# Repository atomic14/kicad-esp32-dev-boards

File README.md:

# ESP Dev-Board Generator

Generates canonical "basic dev board" KiCad schematics for the Espressif modules
that have a **PCB antenna + native USB** (12 modules across S2/S3/C3/C5/C6/H2).
Each board takes a shared skeleton (USB-C, 3V3 LDO, BOOT/EN buttons, LEDs) and
adds the module symbol + two break-out pin headers, wired entirely with net
labels (no routing). Output is a complete, openable KiCad project per module.

> **Why / design rationale:** see [`DECISIONS.md`](DECISIONS.md). This file is
> the *operational* guide; DECISIONS.md is the *why*.

## What it builds

Every board is the same canonical dev board — USB-C, 3V3 LDO, BOOT/EN buttons,
power + user LEDs — plus the module and its full GPIO break-out on two headers
(that's the ESP32-C3-WROOM-02 above; every component carries its 3D model, so
each board renders assembly-ready). The views below are to scale (equal
mm-per-pixel; each label carries the board's WxH):

The back silk labels every header pin with its net name and carries a vertical
board identifier — the module name plus the git revision that generated it
(`git describe --tags --always --dirty`):

These are snapshots of what `make.py --render` writes to `build/`: seven
montages (`montage_{top,top_bare,bottom}[_scale].png` — auto-fit and to-scale —
plus `montage_hero.png`) and a perspective `render_hero.png` per board under
`build/<MODULE>/`. To refresh them:

```bash
cp build/montage_{top,bottom}_scale.png docs/images/
cp build/ESP32-C3-WROOM-02/render_hero.png docs/images/hero.png
```

`make.py --animate` adds the moving version: `build/montage_spin.mp4`, a
2560×1440 grid of all 12 boards each turning a full 360° on a three-quarter
tilt, staggered so the grid reads as a wave. The turn wraps exactly, so it
loops seamlessly. It renders ~1440 frames and takes roughly half an hour —
`--frames`/`--supersample` trade quality for time, and `--boards X --grid 1x1`
renders a single board full-frame.

## Prerequisites (per machine)

1. **KiCad 10.x** installed (the schematics use the v10 file format).
2. **Espressif KiCad libraries installed *for that same KiCad version*** via
   KiCad's **Plug-in & Content Manager** (open KiCad 10 → PCM → search
   "Espressif" → install "Espressif KiCad Libraries" → Apply). This provides the
   `PCM_Espressif` symbol/footprint libraries. *This is the one manual install
   step and must be done before running anything.*
   > ⚠️ The addon is installed **per KiCad major version**. Having it for
   > KiCad 8/9 does **not** count if you run KiCad 10 — the PCM stores each
   > version's addons under a separate `Documents/KiCad/<version>/3rdparty` dir.
   > `resolve_library.py` pins to your running `kicad-cli` version and will
   > **hard-fail** (with these instructions) if the addon is missing for it,
   > rather than silently mixing libraries across versions.
3. **[uv](https://docs.astral.sh/uv/)** (Python package manager).
4. **[KiCadRoutingTools](https://github.com/atomic14/KiCadRoutingTools)** (our
   fork, `dev-board-fixes` branch) cloned as a **sibling** of this repo (or set
   `$KICAD_ROUTING_TOOLS`), with its Rust router built:
   ```bash
   git clone -b dev-board-fixes https://github.com/atomic14/KiCadRoutingTools.git ../KiCadRoutingTools
   (cd ../KiCadRoutingTools && python3 build_router.py --from-source)  # needs cargo
   ```
   Only needed for the *route* stage — build/render/fab work without it.
5. Internet access to `https://www.atomic14.com/esp32/` (only needed when
   curating a new module's `board.yaml`).

`resolve_library.py` auto-locates KiCad on macOS / Linux / Windows. If it can't,
set `ESPRESSIF_3RDPARTY` (the `<kicad>/3rdparty` dir) and/or `KICAD_CLI`
(path to `kicad-cli`) and re-run it. **Re-run it after any KiCad upgrade /
reinstall** — `library.json` records absolute, version-specific paths, and
`make.py` will refuse to run (pointing you back here) if those paths go stale.

## Quick start

```bash
uv sync                                   # restore the Python env (pinned in uv.lock)
uv run python scripts/resolve_library.py  # detect KiCad/libraries -> library.json (once/machine)
uv run python scripts/make.py             # build + route every board (THE command)
```

`make.py` is the one front door — it chains clean → build → route → render:

```bash
uv run python scripts/make.py            # build + route all modules
uv run python scripts/make.py --clean    # wipe prior output first
uv run python scripts/make.py --render    # also render the 3D montages
uv run python scripts/make.py --animate   # also render the spinning montage mp4 (~30 min)
uv run python scripts/make.py --fab       # also export fab zips (Gerbers + drill)
uv run python scripts/make.py --all       # clean + build + route + render + fab
uv run python scripts/make.py --no-route  # build only
```

Generated boards land in `out/<MODULE>/<MODULE>.kicad_sch` (+ `.kicad_pro`,
`.kicad_pcb`); validation artifacts (ERC JSON, PDF render) in `build/<MODULE>/`.
Open any `out/<MODULE>/<MODULE>.kicad_pro` in KiCad. Both `out/` and `build/` are
git-ignored and fully disposable — `make.py --clean` (or `clean.py`) just removes
them. The curated source in `modules/` is never touched.

## Repository layout

```
DECISIONS.md            design decisions + rationale (read for the "why")
library.json            GENERATED per machine by resolve_library.py (git-ignore-able)
pyproject.toml/uv.lock  pinned Python env (kicad-skip, sexpdata, pyyaml)
baseline-left-en/       skeleton KiCad project (INPUT — never edit); EN button on the left
baseline-right-en/      same skeleton mirrored, EN on the right — generator auto-picks per module
  BasicEsp32Footprints.pretty/, 3d-models/, fp-lib-table   project-local footprints + 3D models
scripts/                orchestrators (run these); scripts/lib/ holds the per-module primitives
modules/<MODULE>/        CURATED SOURCE only (committed) — clean never touches it
  board.yaml            the only hand-authored file (see below)
  pinout.json           extracted from the symbol (never hand-edit); cached source
out/<MODULE>/            GENERATED board (git-ignored, disposable: rm -rf out)
  <MODULE>.kicad_sch/pro/pcb   the board — open <MODULE>.kicad_pro in KiCad
  fp-lib-table + *.pretty/ + asset dirs   copied from baseline
  route_debug/          per-stage routing snapshots for inspection
  fab/ + <MODULE>-fab.zip   Gerbers + Excellon drill; the .zip is fab-ready
build/<MODULE>/          GENERATED validation artifacts (git-ignored, disposable)
docs/AGENT_END_TO_END.md  agent spec: curate every board.yaml, then pilot-verify one module
docs/images/             committed montage snapshots referenced by this README

```

## The pipeline (`scripts/`)

**Orchestrators** — the top-level commands you run:

| Script | Role | Deterministic? |
|---|---|---|
| `make.py` | **THE command** — chains clean → build → route → render → fab (flags toggle stages) | ✅ |
| `resolve_library.py` | Find KiCad libs + `kicad-cli` → `library.json` | ✅ run once/machine |
| `build_all.py [--clean]` | extract → build → validate every curated module | ✅ |
| `route_all.py [--no-diff]` | autoroute every board (diff-pair with single-ended fallback; writes back in place) + DRC | ✅ |
| `render_boards.py` | 3D montages of every board → `build/` (top, top-bare/no-components, bottom — each auto-fit AND to-scale — plus a perspective hero shot per board) | ✅ |
| `animate_boards.py` | 2560×1440 mp4 of all 12 boards on 3D turntables → `build/montage_spin.mp4` (seamless 4 s loop; slow, ~30 min) | ✅ |
| `fab_all.py` | Gerber + Excellon drill zip per board → `out/<M>/<M>-fab.zip` | ✅ |
| `clean.py` | remove generated output for a fresh run — just `rm -rf out build`; the curated `modules/` source is never touched | ✅ |

**Primitives** (`scripts/lib/`) — operate on one module; called by the orchestrators, rarely run directly:

| Script | Role |
|---|---|
| `extract_pinout.py "<MODULE>"` | Parse the symbol → `modules/<m>/pinout.json` |
| `footprint_edges.py "<MODULE>"` | Physical pin edges from the footprint |
| `build_board.py "<MODULE>"` | **The generator**: module + perimeter-split headers + labels + footprints + project files (copies the baseline's `fp-lib-table` and all asset dirs — `*.pretty` footprint libs, `3d-models/`, etc.) |
| `route_board.py "<MODULE>"` | Autoroute one board (USB-C fine neck, signals, GND pour) |
| `place_pcb.py` / `gnd_finish.py` / `gnd_prestitch.py` | PCB placement + GND-pour fill/stitch helpers (prestitch protects GND pads before routing) |
| `validate.py <sch>` | ERC delta vs baseline + PDF render |
| `fab_export.py "<MODULE>"` | Gerbers (`--check-zones` refills pours) + Excellon drill → zipped fab package |

**~95% of the work is fully scripted.** The only step needing human/agent
judgement is curating each module's `board.yaml`.

## Adding / re-curating a module

`board.yaml` is the one hand-authored file. Most wiring is auto-derived (power,
GND, EN, USB→D±, GPIO→`GPIOxx` labels). You decide:

- **`do_not_break_out`**: pins that must NOT be exposed — internal flash/PSRAM
  and any pin the [atomic14 module page](https://www.atomic14.com/esp32/modules/)
  marks as a hard "do not use". Strapping / JTAG / UART / USB pins are still
  broken out (documented in `notes`, not excluded).
- **`strapping` / `input_only`**: GPIO numbers (curated from the atomic14 page /
  datasheet) that are sampled at reset or have no output driver. They're *still*
  broken out — these lists only steer the on-board LED away from unsafe pins.
- **`builtin_led`**: the GPIO the skeleton's on-board LED attaches to. The
  generator routes it to the **safe pad physically nearest the LED** on the laid-out
  PCB (shortest trace); `build_board.py pick_builtin_led()` computes exactly that,
  and the build **hard-errors** if `builtin_led` names a strapping / input-only /
  non-broken-out pin. "Safe" = I/O-capable, non-strapping, broken-out GPIO.
- **`boot`**: the download/boot strapping GPIO the on-board BOOT button pulls low —
  GPIO0 on Xtensa (ESP32/-S2/-S3), GPIO9 on most RISC-V (-C3/-C6/-H2), GPIO28 on
  -C5. Varies per module, so the generator aliases the skeleton's `BOOT` net onto it.

```yaml
module: ESP32-S3-WROOM-1
symbol: PCM_Espressif:ESP32-S3-WROOM-1
do_not_break_out: [SPIDQS, SPIIO6, SPIIO7]   # octal flash/PSRAM, must not expose
overrides: {}
strapping: [0, 3, 45, 46]   # sampled at reset — unsafe for the LED (GPIO45 = VDD_SPI)
input_only: []              # no output driver
builtin_led: GPIO48         # safe GPIO pad nearest the on-board LED (NOT GPIO45, a strap)
boot: GPIO0                 # download/boot strapping pin the BOOT button pulls low
notes: >
  Source: https://www.atomic14.com/esp32/modules/esp32-s3-wroom-1/ ...
```

> ⚠️ Curation is **symbol-specific, not name-based**: e.g. `SPIIO6/7`/`SPIDQS`
> are reserved on the octal S3-WROOM-1, but are *freely-usable GPIO* on the quad
> S3-MINI-1 (and are NC, so absent, on the WROOM-2). Check the atomic14 page;
> don't blindly exclude by name.

Then: `uv run python scripts/lib/build_board.py "<MODULE>"` and
`uv run python scripts/lib/validate.py out/<m>/<m>.kicad_sch`, and **open the
rendered PDF** — the visual check catches things ERC can't (it once passed a
board whose USB pins were unconnected).

## Validation

`validate.py` gate = **no new ERROR-severity ERC violations vs the baseline**.
New *warnings* are expected and fine (notably the `pin_to_pin` from connecting
`GPIO0` to the boot button — the EasyEDA button symbol uses `Unspecified` pin
types). The baseline itself has ~58 pre-existing violations, so the bar is the
*delta*, not zero. Always also eyeball the PDF render.

## Fabrication

`make.py --fab` (or `fab_all.py`, or `fab_export.py "<M>"` for one) exports a
fab-ready package per board to `out/<M>/<M>-fab.zip` (loose files also in
`out/<M>/fab/`). The zip holds the standard 2-layer Gerber set (`F.Cu B.Cu`,
paste, silkscreen, mask, `Edge.Cuts`) plus an Excellon drill file, drill map,
and `.gbrjob` — flat-zipped, ready to upload to JLCPCB / PCBWay / most houses.

Key detail: the Gerber export runs with `--check-zones`, which **refills the
copper pours during export**, so the GND plane is always present in the copper
Gerbers even though headless tools save boards with empty fills — otherwise
you'd ship a board with no ground plane. Coordinates use an absolute origin for
both Gerbers and drill so they align. If your fab wants PTH/NPTH drills split,
add `--excellon-separate-th` in `fab_export.py` (currently combined).

**Silk order-number marker.** `build_board` drops a small F-silk text
(`SILK_MARKER_TEXT`, default `"WayWayWay"`) centred in the clear band just above
the module's bottom pin row — under the body, so it's hidden once the module is
soldered down, and never on exposed copper (its real rendered bounding box is
clearance-checked against every pad, and the size auto-shrinks on tight modules).
This gives the board house a designated spot for its order number instead of it
landing on visible silk. Change the text via `SILK_MARKER_TEXT` in `place_pcb.py`.

**Back-silk board identifier.** Each board also gets a vertical B-silk text
centred on the back: `"<module> <git describe --tags --always --dirty>"` — so a
physical board always names its module and the exact repo revision that
generated it. Tag the repo (e.g. `v1.0`) to get a clean rev number on the silk;
between tags it reads `v1.0-3-g<hash>`, and `-dirty` flags uncommitted changes.
The text auto-sizes to the board height (1.5 mm down to a 0.8 mm floor,
dropping the revision before the name if it can't fit) — see
`place_pcb.board_id_text`.

## CI / Releases

`.github/workflows/build.yml` runs the whole pipeline on GitHub Actions
(Ubuntu): KiCad 10 from the official PPA, the Espressif PCM addon unpacked
headlessly into the layout `resolve_library.py` expects, then
`xvfb-run make.py --all`. Every push to `main` uploads the boards as a
workflow artifact; pushing a version tag (`git tag v1.1 && git push --tags`)
additionally publishes a GitHub **release** with the per-board fab zips, KiCad
project zips, and the montages attached. Boards built from a tag carry that
version on their back silk (the identifier bakes in `git describe`).

## Handoff notes

To pass this on: ship the whole directory **except `.venv/`** (regenerated by
`uv sync`) and `library.json`/`out/`/`build/` (regenerated per machine). The
recipient runs the three Quick-start commands. The curated `modules/<M>/board.yaml`
(+ `pinout.json`) are the valuable hand-work and are the only committed per-module
files.

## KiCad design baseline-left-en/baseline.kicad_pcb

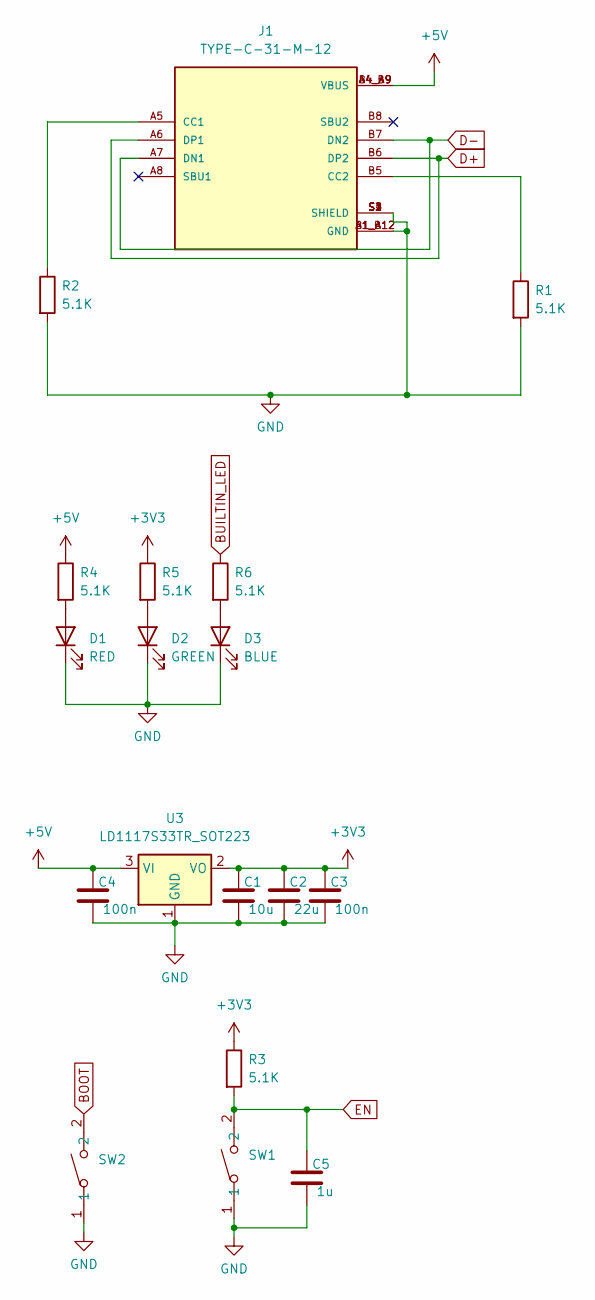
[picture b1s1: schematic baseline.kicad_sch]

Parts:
C1: 10u; C_0603_1608Metric
C2: 22u; C_0603_1608Metric
C3, C4: 100n; C_0603_1608Metric
C5: 1u; C_0603_1608Metric
D1: RED; LED_0603_1608Metric
D2: GREEN; LED_0603_1608Metric
D3: BLUE; LED_0603_1608Metric
J1: TYPE-C-31-M-12; HRO_TYPE-C-31-M-12; PARTREV 2020.12.08
R1, R2, R3, R4, R5, R6: 5.1K; R_0603_1608Metric
SW1, SW2: TS-1088-AR02016; SW-SMD_L3.9-W3.0-P4.45; LCSC Part C720477
U3: LD1117S33TR_SOT223; SOT-223-3_TabPin2

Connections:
+3V3: C1.1, C2.1, C3.1, R3.1, R5.1, U3.2 (VO)
+5V: C4.1, J1.A4_B9 (VBUS), J1.B4_A9 (VBUS), R4.1, U3.3 (VI)
BOOT: SW2.2
BUILTIN_LED: R6.1
D+: J1.A6 (DP1), J1.B6 (DP2)
D-: J1.A7 (DN1), J1.B7 (DN2)
EN: C5.1, R3.2, SW1.2
GND: C1.2, C2.2, C3.2, C4.2, C5.2, D1.1 (K), D2.1 (K), D3.1 (K), J1.A1_B12 (GND), J1.B1_A12 (GND), J1.S1 (SHIELD), J1.S2 (SHIELD), J1.S3 (SHIELD), J1.S4 (SHIELD), R1.2, R2.2, SW1.1, SW2.1, U3.1 (GND)
unnamed: D1.2 (A), R4.2
unnamed: D2.2 (A), R5.2
unnamed: D3.2 (A), R6.2
unnamed: J1.A5 (CC1), R2.1
unnamed: J1.B5 (CC2), R1.1

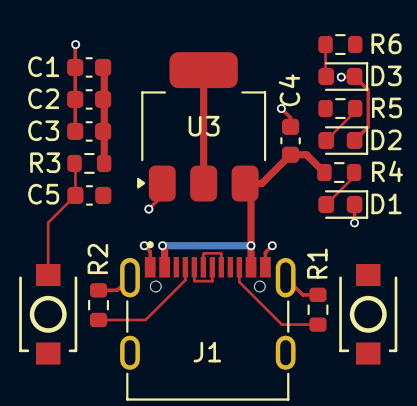
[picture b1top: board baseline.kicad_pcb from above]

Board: 2 copper layers, 18 parts (0 on the bottom side), 11 nets.

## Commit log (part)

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2026-06-25 almost working
2026-06-27 0.4mm power nets
